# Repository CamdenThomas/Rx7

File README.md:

# Rx7

The record of one 1982 Mazda RX-7: every fact about the car and every project on it, as
self-describing CSV, checked by one tool, read and answered through one app.

```
python tools/rx7.py status
```

- **`CLAUDE.md`** — the entire instruction set for any agent working here. No skills,
  no slash commands, no second document.
- **`tools/rx7.py`** — the only tool. Stdlib Python. `check` is the gate: exit 1 means
  the record contradicts itself, and it is the only thing that can stop a commit.
  `status` prints READY and BLOCKED per area — what can be started now, and what each
  waiting row waits on. `export` is the whole record as JSON for the app; `answer` is the
  one writer of Camden's answers. `selftest` tests the gate resolver and that writer.
- **The Rx7 app** (`02-APP/app/`) — a desktop app for each desk the tree is cloned to
  (Fedora, the Mac) and an Android app for the phone, one design. It shows the car, the projects, the open blocks,
  parts picks, work lists and every decision, and it is where Camden answers. It keeps no
  fact of its own. Its README says how to build and install it.
- **`.github/workflows/rx7.yml`** — CI backstop, `selftest` + `check`, for the clone
  where the hook was never installed.

Areas: `00-CAR` (the car as it stands, and every truth about it), `02-APP` (the app),
`02-PROJECTS/*` (work in flight), `99-ARCHIVE` (finished process, and the v2 view layer this
version replaced). The source files themselves (manuals, catalogues, datasheets) are kept out of git in
`00-CAR/library`, the found 3D models in `02-PROJECTS/03-cad/model` (D-573).

There are no Markdown pages to read or to write in (D-405): blocks, answers, picks, the
TODO lists and every decision's text live in the record, and the app shows them. The only
generated files are the harness-leg drawings (`rx7.py diagrams`, D-385).

One-time per clone: `git config core.hooksPath .githooks`

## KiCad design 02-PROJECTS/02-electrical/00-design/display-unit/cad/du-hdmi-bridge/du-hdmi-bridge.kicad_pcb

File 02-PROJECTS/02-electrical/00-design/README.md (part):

# 00-design — drawn and written by hand, outside the record

*Rev 2026-10-15 (D-611: the parts, each holding its own cad, data, diagrams and firmware; every script
in tools/ · D-612: the boxes' part folders, the CAD marked outdated by the overhaul) · owns: the boundary between this folder and the record, what each folder in it is, and the
rules for the drawings and the code. It lives inside `02-electrical`, which owns every part drawn here.*

## Contents

1. The folders · 2. The fence · 3. Version and the bring-up log · 4. The boards · 5. Why a
schematic at all · 6. Checking the sheets against the record · 7. The firmware · 8. Building the
simulator · 9. Building for the Teensy · 10. What the renderer guarantees · 11. The bench
stages · 12. The bench mule · 13. The design in 3D for the app

---

## 1 · The folders (D-496, D-497, D-611)

One folder per part, each holding the same four kinds of thing, and four shared folders. The parts
are the boxes of the record's `boxes` table (D-612) - the PMU box, the DU, the CU (the CUR is a part
of the CU and sits inside it), the bin box, the bay junction and the amplifier dock - and the
harness. Paths in this README are from this folder.

> **The CAD is outdated by the overhaul (D-612).** The record now holds the boxes, their plugs and
> cavities and the PMU box's connections; every board, mock-up and enclosure below is the last drawn
> state from before it, kept until its CAD-pass row redraws it (Y69 to Y75, the 3D Y77). The pass's
> brief is `diagrams/overhaul-plan.html`. Each part's `diagrams/` holds its **plan sheet**, `<box>-plan.svg`,
> drawn from the record by `rx7.py diagrams` (D-613): that is the current plan; a CAD drawing still
> carries an orange OUTDATED banner (`tools/stamp_outdated.py`).

```
00-design/
├── control-unit/                 THE CONTROL UNIT (CU)
│   ├── cad/                      cu-carrier (KiCad), cu-face-board (KiCad), cu-assembly (the whole unit, FreeCAD)
│   ├── data/                     the boards' BOMs and fab BOMs, their extracts (*-board.json, *-probe.json),
│   │                             the assembly's and the enclosures' parameter tables (*_params.py)
│   ├── diagrams/                 schematic SVGs, renders, assembly drawings, the assembly's views, the face concept
│   ├── firmware/                 cu
│   └── control-unit-remote/      THE CUR, a part of the CU
│       ├── cad/                  cur-board (KiCad), cur-assembly (FreeCAD)
│       ├── data/                 its BOM, its assembly's parameter table
│       └── diagrams/             its schematic, renders, views, the face concept
├── display-unit/                 THE DISPLAY UNIT (DU)
│   ├── cad/                      du-carrier (KiCad), du-hdmi-bridge (KiCad), du-assembly (FreeCAD)
│   ├── data/                     as the CU's
│   ├── diagrams/                 as the CU's
│   ├── firmware/                 du, du_radio, du_sim, tach_simulator
│   └── vendor/                   Bridgetek's ME817EV datasheet (S-500)
├── pmu/                          THE PMU BOX (D-596 to D-610): the PMU, its smart switches, fuses and
│   │                             wake circuit, and at the swap the ECU - its contents in the record (D-612)
│   ├── cad/                      (its board, enclosure and mock-up, Y69)
│   ├── data/                     (its parameter tables, Y69)
│   ├── diagrams/                 (its drawings)
│   ├── firmware/                 pmu_sim (the bench stand-in), ladder_decode_test
│   └── vendor/                   ECUMaster's manual, pinout and CAD package with the STEP (S-027, S-028, S-029)
├── bin-box/                      THE BIN BOX beside the battery (D-608, D-609): cad, data, diagrams - Y73
├── bay-junction/                 THE BAY JUNCTION, the jump post and power junction (D-609): cad, data, diagrams - Y74
├── amp-dock/                     THE AMPLIFIER DOCK and its upmix board (D-609): cad, data, diagrams - Y75
├── harness/
│   ├── cad/connectors/, devices/ what the harness's connectors and devices are drawn from (READMEs; §13)
│   ├── data/                     (reserved)
│   └── diagrams/                 the harness-leg drawings, generated by rx7.py diagrams (D-385)
├── data/                         what the parts share: pin_tables.csv (the vendor pin tables check.py
│                                 holds every symbol to) and the bench order's three cart files
├── diagrams/                     what spans the parts: overhaul-plan.html, the CAD pass's brief (D-612), and
│                                 boxes-plan.svg, the boxes' overview (drawn by rx7.py diagrams, D-613)
├── tools/                        every script (below)
├── tests/                        the host suites and run.sh, which test every part together (tests/README.md)
└── sim/                          the ngspice decks (sim/README.md)
```

**Where a file goes.** A KiCad project or a FreeCAD model, and what is generated from it to be
built (the gerbers and their zip in `cad/<board>/fab/`, STEP, STL, FCStd), is `cad/`. Anything a
tool reads or writes as data - a BOM, a board's extract, a parameter table, a report - is `data/`.
Anything read by eye - SVG, PNG, HTML - is `diagrams/`. No file is in two places: a BOM exported
from a sheet, a fab BOM built from it by `fab_bom.py`, a cart written by `bench_cart.py` each say
in their tool which file they come from.

**The tools** (`tools/`, every one finds a part's files through `parts.py`, where the layout is
written once):

| Script | What it does |
|---|---|
| `parts.py` | the layout: each part's folder, each board's and assembly's files |
| `check.py` | holds every sheet to the record and to `data/pin_tables.csv` (§6) |
| `mockup.py`, `mockup_selftest.py` | build or self-test one unit's mock-up: `freecadcmd tools/mockup.py --pass du-assembly` |
| `du_assembly.py`, `cu_assembly.py`, `cur_assembly.py` | each unit's mock-up geometry, from its `<part>/data/<name>_params.py` |
| `enclosure.py`, `enclosure_lib.py`, `enclosure_extract.py` | a board's enclosure (Y7) from `<part>/data/<board>_enclosure_params.py`; the board extract it reads |
| `du_hdmi_bridge_sch.py` / `_pcb.py`, `cur_board_sch.py` / `_pcb.py` | the two boards drawn by script: the sheet, then the board |
| `fabpack.py`, `assembly.py`, `fab_bom.py`, `bench_cart.py` | a board's fab package, its assembly drawings, its fab BOM against its sheet and the carts, the carts |
| `stamp_outdated.py` | the OUTDATED banner on a CAD drawing the overhaul made stale (D-613); `--clear` takes it off, a re-export drops it |
| `export_glb.py`, `export_glb_fc.py`, `harness_connectors.py`, `harness_devices.py`, `harness_devices_fc.py` | the design in 3D for the app (§13) |

Names (D-611): the DU, CU, CUR and PMU name every folder, project and sketch here; the record's
ids are unchanged (D-496: the module ids ICU and DCU, `icu_channels`, `dcu_channels`, the CAN
senders and the firmware's own identifiers), and only the words a tool prints or a drawing shows
say DU and CU.

## 2 · The fence

**This is not the visual layer.** CLAUDE.md §1 and §9 say the tree has exactly one
generated document and that the visual layer of the record is a separate, later concern
that must not be started yet. Nothing in the CAD is generated, nothing in here renders the
record, and nothing in the drawings reads a CSV at build time. The CAD is a tool being used to
draw circuit boards, in the same category as the firmware — engineering artefacts for one
component, not a view of the design.

The fence, in full:

- **This folder is not an area.** No `data/_tables.csv`, so `rx7.py` does not see it
  at all: `areas()` cannot find it, `check` never reads it, and nothing here can make the
  record invalid or be made invalid by it. It sits in `02-electrical/`, beside `data/`, and
  never inside it (the CAD moved here 2026-09-23, D-386).
- **The boards live in their parts (D-496, D-497, D-611).** The Control Unit's (`control-unit/cad/`:
  the CU carrier, the face board and the unit's mock-up; the CUR's board and mock-up in
  `control-unit/control-unit-remote/cad/`) and the Display Unit's (`display-unit/cad/`: the DU
  carrier, the HDMI bridge and the unit's mock-up) are drawn under this same fence; `tools/` keeps
  every script and `data/` what the parts share.
- **The record wins, always.** If a schematic and a row disagree, the row is right and the
  drawing is stale. Nothing in `../data/` cites a file in here as evidence.
- **A fact worth keeping is promoted, not linked** — it becomes a row, and the drawing
  becomes an illustration of the row.
- **Who draws (D-453).** Camden ruled on 2026-09-12 that he would draw these himself to learn
  KiCad; D-453 lifts that, and the agent draws, lays out and checks the boards too. They are
  still not a view layer: if one starts to look like it, delete it, don't grow it.
- **The firmware is a source of truth** (R6). `display-unit/firmware/du/cluster_core.h` defines
  the palette, every layout constant, the icon set, unit conversions and sensor-fault rendering
  (D-151…D-158). `display-unit/firmware/du/stats.h` owns the automated trip and lifetime figures
  (D-163). `display-unit/firmware/du/can_map.h` is the machine-readable CAN map. The prose
  documents describe *why*; this code defines *what*. It owns, in code: cluster layout, palette,
  rendering, CAN structs and the automated trip figures.

## 3 · Version and the bring-up log

`ICU_FW_VERSION` in `display-unit/firmware/du/du.ino`, `DCU_FW_VERSION` in
`control-unit/firmware/cu/cu.ino` and `PMU_SIM_VERSION` in `pmu/firmware/pmu_sim/pmu_sim.ino`,
printed at boot. Bump it on any behaviour change, log it in `../data/bringup_log.csv`
(`rx7.py add 02-PROJECTS/02-electrical bringup_log …`), tag the commit.

## 4 · The boards

| Project | What | Status |
|---|---|---|
| `control-unit/cad/cu-assembly/` | The Control Unit (D-479, D-480; its box stepping up behind the face, D-604): a parametric FreeCAD mock-up of its insides and its case - face, panel board, DCU carrier, upper connector board, four DT13s in two rows | **OUTDATED by the overhaul (D-612): redrawn at Y70.** **mock-up built, fit check clear, self-test 57 of 57 (2026-10-15)** - one table of numbers (`control-unit/data/cu_assembly_params.py`), built by `tools/mockup.py --pass cu-assembly`, nothing measured (R11); not the print-ready model (F1) |
| `control-unit/control-unit-remote/cad/cur-assembly/` | The Control Unit Remote (D-586, D-602, D-615): the CUR board behind the ruled 43.11 x 32 face in a two-part case - a front shell (faceplate and walls) with a ledge the board rests on, caps with flanges, the encoder's bushing through the face, a rear cover whose posts hold the board and whose grommet takes the pigtail to the inline DRC 24 | **mock-up built, fit check clear, self-test 13 of 13 (Y71, 2026-10-15)** - shell 41.91 x 30.8, 19.6 deep (30.7 with the knob), 7.7 cm3 ASA; one table of numbers (`control-unit/control-unit-remote/data/cur_assembly_params.py`), built by `tools/mockup.py --pass cur-assembly`; nothing measured (R11) |
| `display-unit/cad/du-assembly/` | The ICU as one unit (D-491): a parametric FreeCAD mock-up - the 12.3-inch display behind its bezel, the display plate with the BT817 board and the chain-ii driver boards, the ICU carrier behind (or under) them with the radio's RF window, the page button, DP-ICU-A / -B in the rear plate | **OUTDATED by the overhaul (D-612): redrawn at Y72.** **mock-up built, fit check clear, self-test 34 of 34 (2026-10-15)** - one table of numbers (`display-unit/data/du_assembly_params.py`); 335 x 136.5 face, 206.6 deep with plugs (182.5 carrier below); nothing measured (R11), `C4` / `M-1` the envelope; not the print-ready model (F1) |
| `display-unit/cad/du-carrier/` | The ICU carrier board as a KiCad 10 schematic, plus its Teensy socket footprint | **OUTDATED by the overhaul (D-612): redrawn at Y72.** **provisional board placed, routed, poured and 3D-modelled, DRC clean (F9 / F10, 2026-10-09)** — 110 × 80 mm is `confirm` until `C4` / `F11`; guide step 8 reached, the fit test is `F11`; sheet and board rev 0.04 (`Y42`, 2026-10-13: the two TVS diodes turned to their mark, the tach zener's cathode joined, C1 68 µF 63 V - its README) |
| `display-unit/cad/du-hdmi-bridge/` | The display bridge board (`P119`, Y46, D-550, D-561): a TI TFP410 from the BT817 board's 50-way flat cable (J1 pin k = CN1 pin 51-k, a type-A cable) to an HDMI socket for the panel kit's driver board; 5 V in, AP2112K-3.3; drawn and routed by `tools/du_hdmi_bridge_sch.py` / `tools/du_hdmi_bridge_pcb.py` (freerouting) | **rev 0.01, 62 x 46 mm two layers, ERC 0, DRC 0 / 0 / 0** - its place in the unit and its 5 V source not drawn, confirm; ordered at Y48 |
| `control-unit/cad/cu-carrier/` | The DCU carrier (`H-002`) | **OUTDATED by the overhaul (D-612): redrawn at Y70.** **provisional board placed, routed, poured and 3D-modelled, DRC clean (Y5, 2026-10-09)** — every pin in `dcu_channels.teensy_pin`, the slow lines on a TCA9539-Q1; 180 × 80 mm is `confirm` until `V-102` and luxury `W-332`; `Y11` (2026-10-09) drew the open blocks' worst case DNP: a second expander, the A/C clutch stage and pressure ADC, the radar alert input, the third comfort ground; rev 0.04 carried the 26-way ribbon header (D-458): `Y12` (2026-10-11) re-laid the top-left block for it, H1 now at (4, 15); sheet and board rev 0.05 (`Y42`, 2026-10-13: Q3 on a SOT-23's real pins, the four TVS diodes turned to their mark, C1 / C8 / C29 68 µF 63 V - its README) |
| `control-unit/cad/cu-face-board/` | The Control Unit's face board (`H-008`, D-492; the face itself D-602): the centre encoder with push, the screen's header, four keys and two window switches on a 4 × 3 matrix, two seat encoders, the IS31FL3236A with 24 LEDs, the 26-way ribbon `J1` and the left plate's 2 × 6 header `J3` | **OUTDATED by the overhaul (D-612): redrawn at Y70.** **rev 0.04 provisional board drawn, routed and poured to D-492 (Y20, 2026-10-13)** — ERC 0, DRC 0 / 0 / 0 parity, `check.py --board cu-face-board` 0 mismatches; 180 × 84.76 from the mock-up, `confirm` until `V-113`; the window switches drawn DPDT (the record's DRV up / down share no row or column) and the screen's supply left to `JP1`, both in its README; no processor (D-355), ordered with the DCU's (D-459) |
| `99-ARCHIVE/2026-10-15_upper-board/` | The upper connector board (`P195`), dropped by D-582 when the CU took one header | **archived 2026-10-15 (D-611)** - its sheet, board and fab package kept there as they were |
| `control-unit/control-unit-remote/cad/cur-board/` | The CUR board (`P198`, D-597, D-602, D-604, D-615): 38.11 x 27.0, four layers (In1 GND, In2 +5V_PNL planes), every switch on its cap's centre - the hazard, both winks, the hatch and fuel-door keys, a 4-way mirror switch, a 9 mm encoder; an IS31FL3218 (0x54) and a PCA9555 (0x20) on its AP2112K; the pigtail's nine pads, DP-CUR pin for pin; drawn whole by `tools/cur_board_sch.py` / `_pcb.py` | **rev 1.00 (Y71, 2026-10-15)** - ERC 0, DRC 0 / 0 unconnected / 0 parity, `check.py --board cur-board` 26 checks 0 mismatches; fab package (16 files) in `cad/cur-board/fab/`; every part a class with a placeholder footprint, `confirm` (R11) |
| `tools/enclosure.py`, `tools/enclosure_lib.py`, `tools/enclosure_extract.py` | The three boards' enclosures (cu-carrier, cu-face-board, du-carrier) as parametric FreeCAD builds: `enclosure_extract.py <board>` writes `<part>/data/<board>-board.json` from the board, `freecadcmd tools/enclosure.py --pass <board>` builds base, DT13 plate and lid (ASA, TE 114-151046 cut-outs, lid gasket groove) from `<part>/data/<board>_enclosure_params.py` into `cad/<board>/enclosure/`, caches `<board>-probe.json`, and fit-checks them against the board STEP; rc 0 = clear | **OUTDATED by the overhaul (D-612): redrawn at Y69 to Y72.** **built on the provisional outlines, fit check clean (Y7, 2026-10-09)** — envelopes `C4` / `V-102` / `V-113` are parameters, `confirm`; STEP / STL outputs are generated and ignored; rebuilt at `F11`, printed at `F1` (CK27) |

**Layout is in, as of 2026-09-21 (D-361).** Camden asked for the full PCB and 3D guide for both
boards, which lifts `display-unit/cad/du-carrier/README.md`'s old "schematic yes, PCB not yet"
(ICU layout was already his step `F2`). Board layout and the 3D model are part of the CAD's job
now. **Ordering boards is still his, and still money** (`F2` for the ICU, `F5` for the DCU), and
nothing in here orders anything. Both boards are this build's (D-374): their specs are
`../data/icu_channels.csv` and `../data/dcu_channels.csv`. Only the loads the DCU drives are the
luxury package's.

## 5 · Why a schematic at all

The analog front end is currently only describable in prose. `icu_channels.csv` row IC01
carries, in its stage column, *"100 Ω 1 W pull-up from the carrier's 5 V behind jumper J1
(fitted) → node → 15 kΩ / 10 kΩ divider (×0.4, 5 V → 2.0 V) → 100 nF → BAT54S to 3V3 /
GND"*. That is precise, complete, and unreviewable — nobody can read that sentence and see
that a clamp is on the wrong side of a resistor. Drawn, it is one glance.

That is the whole argument, and it is narrow. It does not extend to the harness: wire
gauge, colour, bundles, cavities and cut lengths are the record's job and KiCad has no
model for any of them.

And it earned that on the first attempt, which belongs here where the argument is made: drawing
IC01 turned up that **every BAT54S clamp on the board was the wrong way round** - anode to +3V3 and
cathode to ground. The sentence above is silent on direction and reads perfectly either way round.
The picture is not.

## 6 · Checking the sheets against the record (`tools/check.py`, Y3)

`python3 tools/check.py` (from this folder, or from anywhere; `-v` for every pass and the walk it took, `--board du-carrier|cu-carrier|cu-face-board|cur-board`, `--netlists DIR` to reuse exports) runs `kicad-cli sch export netlist` on each sheet, one at a time, and holds the drawing to the record: every pin in `icu_channels.teensy_pin` and `dcu_channels.teensy_pin` on its socket pad and named net, reaching the part the record says (the XIAO's TX, the transceiver's STB, the expander's ports); every `at_the_drop` cavity wired on the board-edge connector and walked through the board to that channel's processor pin; the ribbon against `panel_ribbon` on both boards, with the keys, encoders and thumbstick pins that hang off each conductor and the matrix diodes' direction; `CONVENTIONS.md` §5 (the rails never meet, every BAT54S the right way round); and each functional-block symbol's pin numbers against the vendor pin tables in `data/pin_tables.csv` (part, package, pin, name, source URL and page). On the upper connector board (archived 2026-10-15), which had no processor, every cavity of `DP-DCU-D` and `DP-DCU-E` is held to its `state` (wired, or bare behind a plug), to a net of its own, and to what its `src_note` names: the header for the carrier's J6-J8 / J5 / J3 lead pin for pin, or the `panel_ribbon` line, named as that line. It prints one `board:ref:pin expected X got Y` line per disagreement and a summary line per board; exit 0 clean, 1 any mismatch, 3 kicad-cli missing or a sheet unreadable. `tests/run.sh` runs it after the can_map check, so a schematic that disagrees with the record fails the test suite (skipped with a notice when kicad-cli is absent). The record wins: a mismatch is fixed on the sheet, or in `data/pin_tables.csv` from the datasheet, never by editing the check to pass.

**Transistors and diodes are held to a pin table too (Y42, 2026-10-13).** Pricing the bench order turned up three of one kind on the two carriers, each found by hand: the DCU's Q3 drawn gate / drain / source on a SOT-23 (every SOT-23 FET is gate, source, drain), the ICU's zener D20 with its cathode on the package's unused pin, and six one-way TVS diodes drawn with two anodes, the footprint's cathode mark on ground. So a `Q` is checked against `pin_tables.csv` as a `U` is, with a note if it has no table, and a `D` is checked when a table names its value (the one-way TVS: pin 1 the cathode, the end KiCad's footprint marks). Run on the sheets as they were, it refuses all three (the old Q3 only once its part is named). Counts with it, 2026-10-15: du-carrier 105, cu-carrier 172, cu-face-board 79, cur-board 31.

The left plate's wink check (`check_winks`, Y22, D-499 / D-504) is read from the record too: `J2`'s pins against the `L3-S1` cavities that land on J2 (each wink's NC and common on the pin the row names), the commons off the plate's GND and every J1 net, and one resistor from each switch's NO to J2 pin 3 at the value cavity 11's text gives. No number is typed in it; swapped pins and a wrong value were each refused when tried.

First run, 2026-10-09: every record pin on every sheet matched. The 106 mismatches it reports are all pin-table ones on the DCU - U5-U8 BTS3011TE, U9 BTT6050, U10 BTT6200 and U11 DRV8962 still carry functional-block pin numbers (Y5 redraws them on their real packages) - and the ICU's U8 XIAO, whose symbol has EN and BOOT pins the module does not expose as castellations (IC24).

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
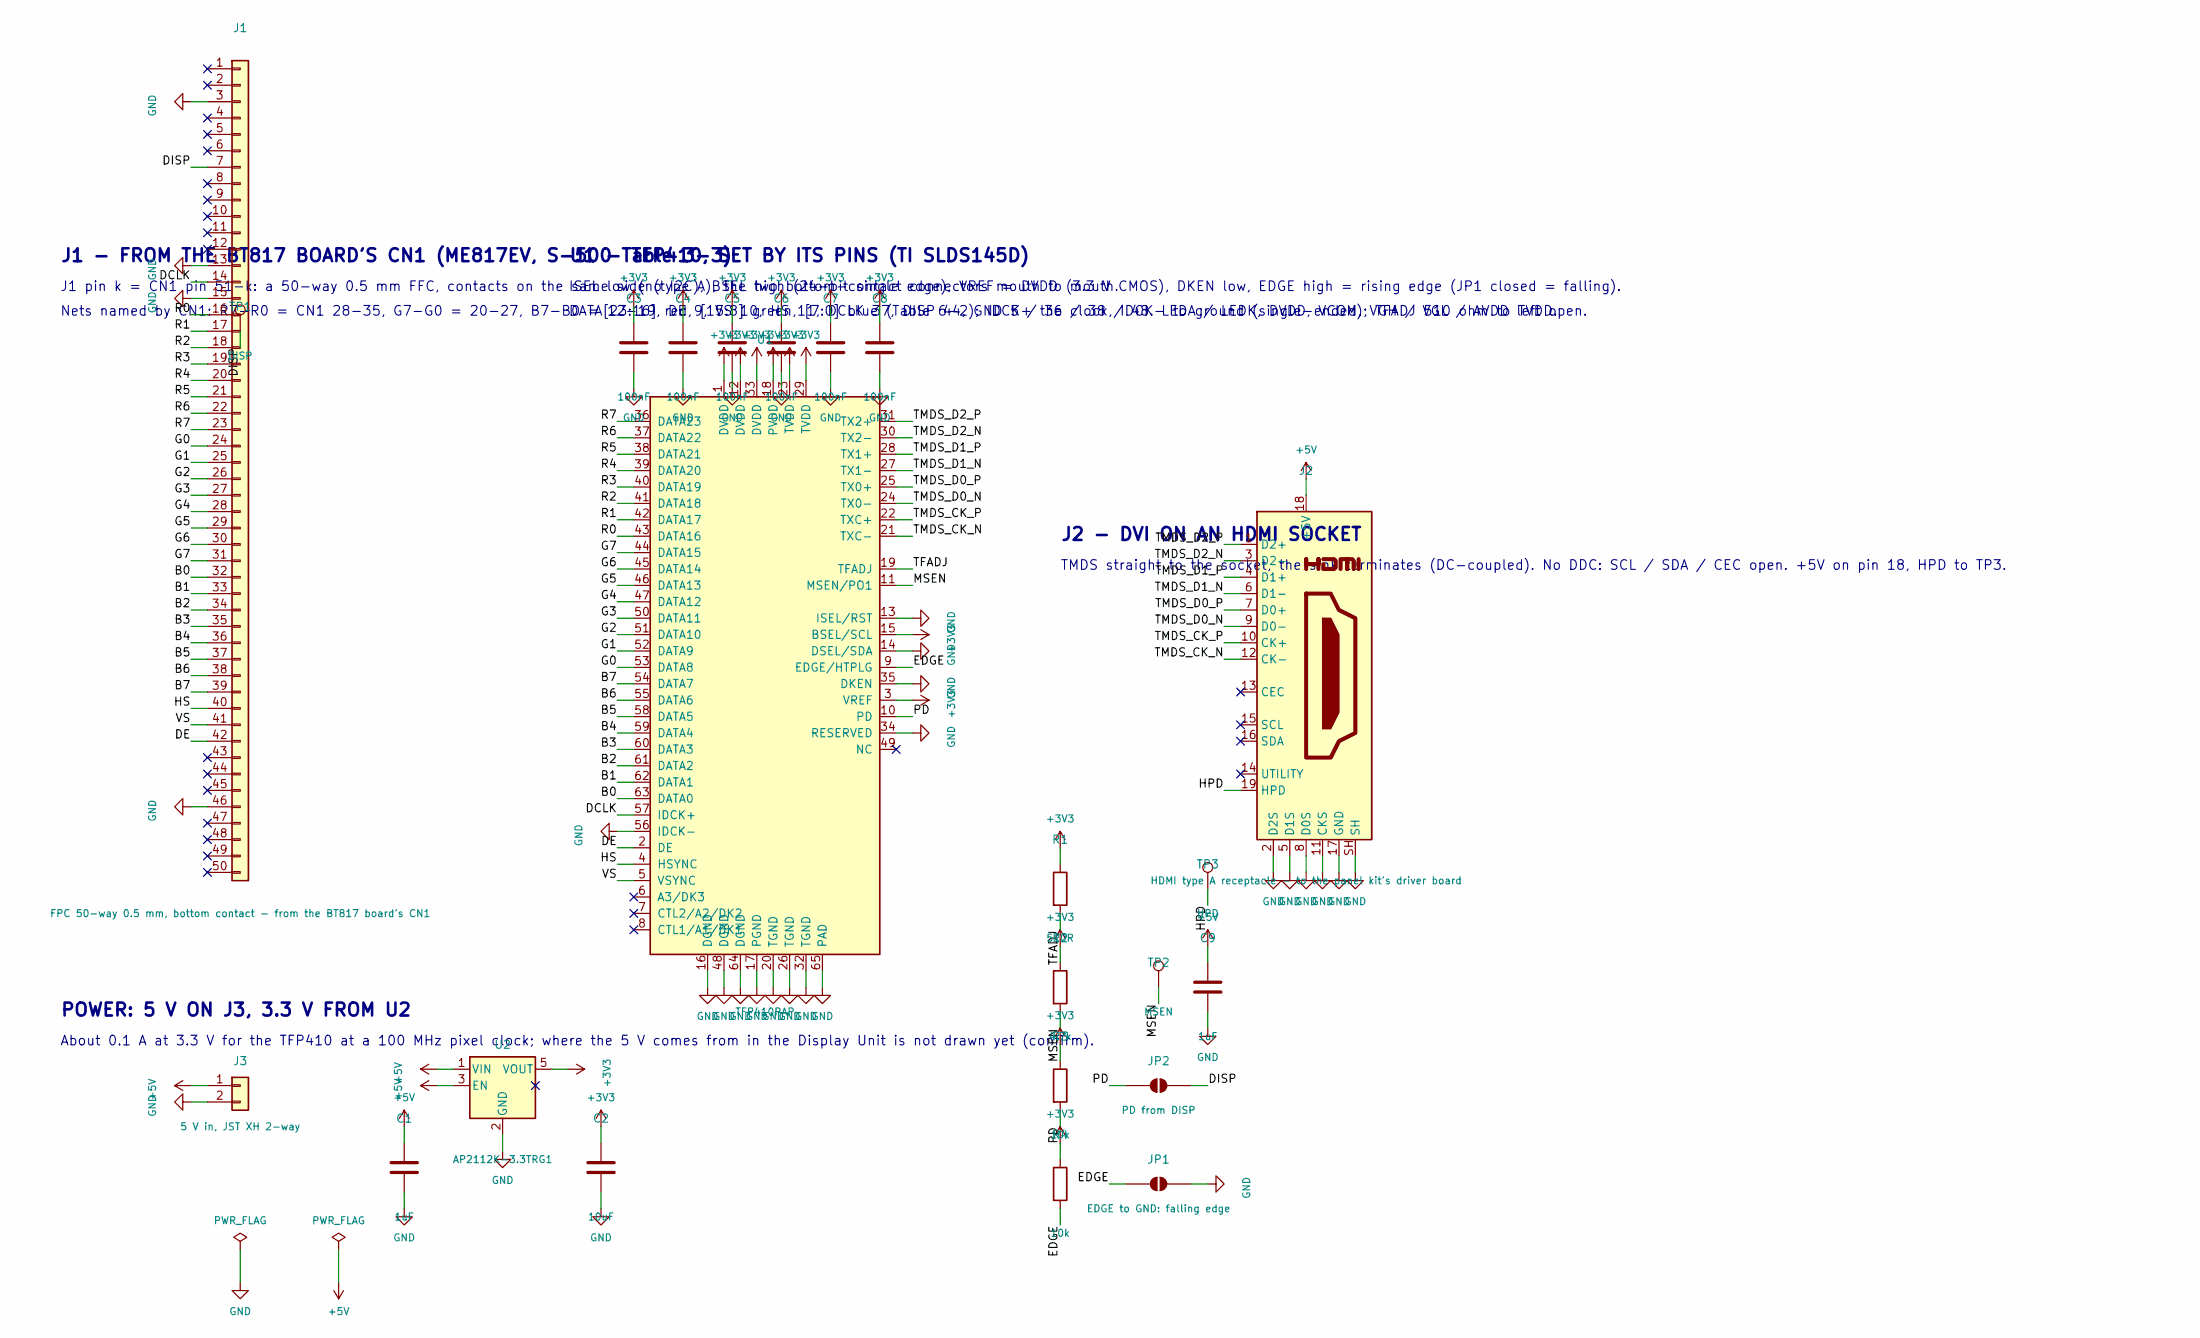
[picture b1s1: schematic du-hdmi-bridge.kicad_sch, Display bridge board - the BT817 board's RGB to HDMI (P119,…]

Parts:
C1, C9: 1uF; C_0603_1608Metric
C2: 10uF; C_0805_2012Metric
C3, C4, C5, C6, C7, C8: 100nF; C_0603_1608Metric
J1: FPC 50-way 0.5 mm, bottom contact - from the BT81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; Hirose_FH12-50S-0.5SH_1x50-1MP_P0.50mm_Horizontal
J2: HDMI type A receptacle - to the panel kit's drive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; HDMI_A_Molex_208658-1001_Horizontal
J3: 5 V in, JST XH 2-way; JST_XH_B2B-XH-A_1x02_P2.50mm_Vertical
JP1: EDGE to GND: falling edge; SolderJumper-2_P1.3mm_Open_RoundedPad1.0x1.5mm
JP2: PD from DISP; SolderJumper-2_P1.3mm_Open_RoundedPad1.0x1.5mm
R1: 510R; R_0603_1608Metric
R2: 4.7k; R_0603_1608Metric
R3, R4: 10k; R_0603_1608Metric
TP1: DISP; TestPoint_Pad_D1.0mm
TP2: MSEN; TestPoint_Pad_D1.0mm
TP3: HPD; TestPoint_Pad_D1.0mm
U1: TFP410PAP; Texas_TQFP-64-1EP_10x10mm_P0.5mm_EP8x8mm_Mask4.44x4.44mm
U2: AP2112K-3.3TRG1; SOT-23-5

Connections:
+3V3: C2.1, C3.1, C4.1, C5.1, C6.1, C7.1, C8.1, R1.1, R2.1, R3.1, R4.1, U1.1 (DVDD), U1.3 (VREF), U1.12 (DVDD), U1.15 (BSEL/SCL), U1.18 (PVDD), U1.23 (TVDD), U1.29 (TVDD), U1.33 (DVDD), U2.5 (VOUT)
+5V: C1.1, C9.1, J2.18 (+5V), J3.1, U2.1 (VIN), U2.3 (EN)
/B0: J1.32, U1.63 (DATA0)
/B1: J1.33, U1.62 (DATA1)
/B2: J1.34, U1.61 (DATA2)
/B3: J1.35, U1.60 (DATA3)
/B4: J1.36, U1.59 (DATA4)
/B5: J1.37, U1.58 (DATA5)
/B6: J1.38, U1.55 (DATA6)
/B7: J1.39, U1.54 (DATA7)
/DCLK: J1.14, U1.57 (IDCK+)
/DE: J1.42, U1.2 (DE)
/DISP: J1.7, JP2.2 (B), TP1.1
/EDGE: JP1.1 (A), R4.2, U1.9 (EDGE/HTPLG)
/G0: J1.24, U1.53 (DATA8)
/G1: J1.25, U1.52 (DATA9)
/G2: J1.26, U1.51 (DATA10)
/G3: J1.27, U1.50 (DATA11)
/G4: J1.28, U1.47 (DATA12)
/G5: J1.29, U1.46 (DATA13)
/G6: J1.30, U1.45 (DATA14)
/G7: J1.31, U1.44 (DATA15)
/HPD: J2.19 (HPD), TP3.1
/HS: J1.40, U1.4 (HSYNC)
/MSEN: R2.2, TP2.1, U1.11 (MSEN/PO1)
/PD: JP2.1 (A), R3.2, U1.10 (PD)
/R0: J1.16, U1.43 (DATA16)
/R1: J1.17, U1.42 (DATA17)
/R2: J1.18, U1.41 (DATA18)
/R3: J1.19, U1.40 (DATA19)
/R4: J1.20, U1.39 (DATA20)
/R5: J1.21, U1.38 (DATA21)
/R6: J1.22, U1.37 (DATA22)
/R7: J1.23, U1.36 (DATA23)
/TFADJ: R1.2, U1.19 (TFADJ)
/TMDS_CK_N: J2.12 (CK-), U1.21 (TXC-)
/TMDS_CK_P: J2.10 (CK+), U1.22 (TXC+)
/TMDS_D0_N: J2.9 (D0-), U1.24 (TX0-)
/TMDS_D0_P: J2.7 (D0+), U1.25 (TX0+)
/TMDS_D1_N: J2.6 (D1-), U1.27 (TX1-)
/TMDS_D1_P: J2.4 (D1+), U1.28 (TX1+)
/TMDS_D2_N: J2.3 (D2-), U1.30 (TX2-)
/TMDS_D2_P: J2.1 (D2+), U1.31 (TX2+)
/VS: J1.41, U1.5 (VSYNC)
GND: C1.2, C2.2, C3.2, C4.2, C5.2, C6.2, C7.2, C8.2, C9.2, J1.3, J1.13, J1.15, J1.46, J2.2 (D2S), J2.5 (D1S), J2.8 (D0S), J2.11 (CKS), J2.17 (GND), J2.SH, J3.2, JP1.2 (B), U1.13 (ISEL/RST), U1.14 (DSEL/SDA), U1.16 (DGND), U1.17 (PGND), U1.20 (TGND), U1.26 (TGND), U1.32 (TGND), U1.34 (RESERVED), U1.35 (DKEN), U1.48 (DGND), U1.56 (IDCK-), U1.64 (DGND), U1.65 (PAD), U2.2 (GND)

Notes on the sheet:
J1 - FROM THE BT817 BOARD'S CN1 (ME817EV, S-500 Table 3-3)
J1 pin k = CN1 pin 51-k: a 50-way 0.5 mm FFC, contacts on the same side (type A), the two bottom-contact connectors mouth to mouth.
Nets named by CN1: R7-R0 = CN1 28-35, G7-G0 = 20-27, B7-B0 = 12-19, DE 9, VS 10, HS 11, DCLK 37, DISP 44, GND 5 / 36 / 38 / 48. LEDA / LEDK, DVDD, VCOM, VGH / VGL / AVDD left open.
U1 - TFP410, SET BY ITS PINS (TI SLDS145D)
ISEL low (no I2C), BSEL high (24-bit single edge), VREF = DVDD (3.3 V CMOS), DKEN low, EDGE high = rising edge (JP1 closed = falling).
DATA[23:16] red, [15:8] green, [7:0] blue (Table 6-2); IDCK+ the clock, IDCK- to ground (single-ended); TFADJ 510 ohm to TVDD.
J2 - DVI ON AN HDMI SOCKET
TMDS straight to the socket, the sink terminates (DC-coupled). No DDC: SCL / SDA / CEC open. +5V on pin 18, HPD to TP3.
POWER: 5 V ON J3, 3.3 V FROM U2
About 0.1 A at 3.3 V for the TFP410 at a 100 MHz pixel clock; where the 5 V comes from in the Display Unit is not drawn yet (confirm).

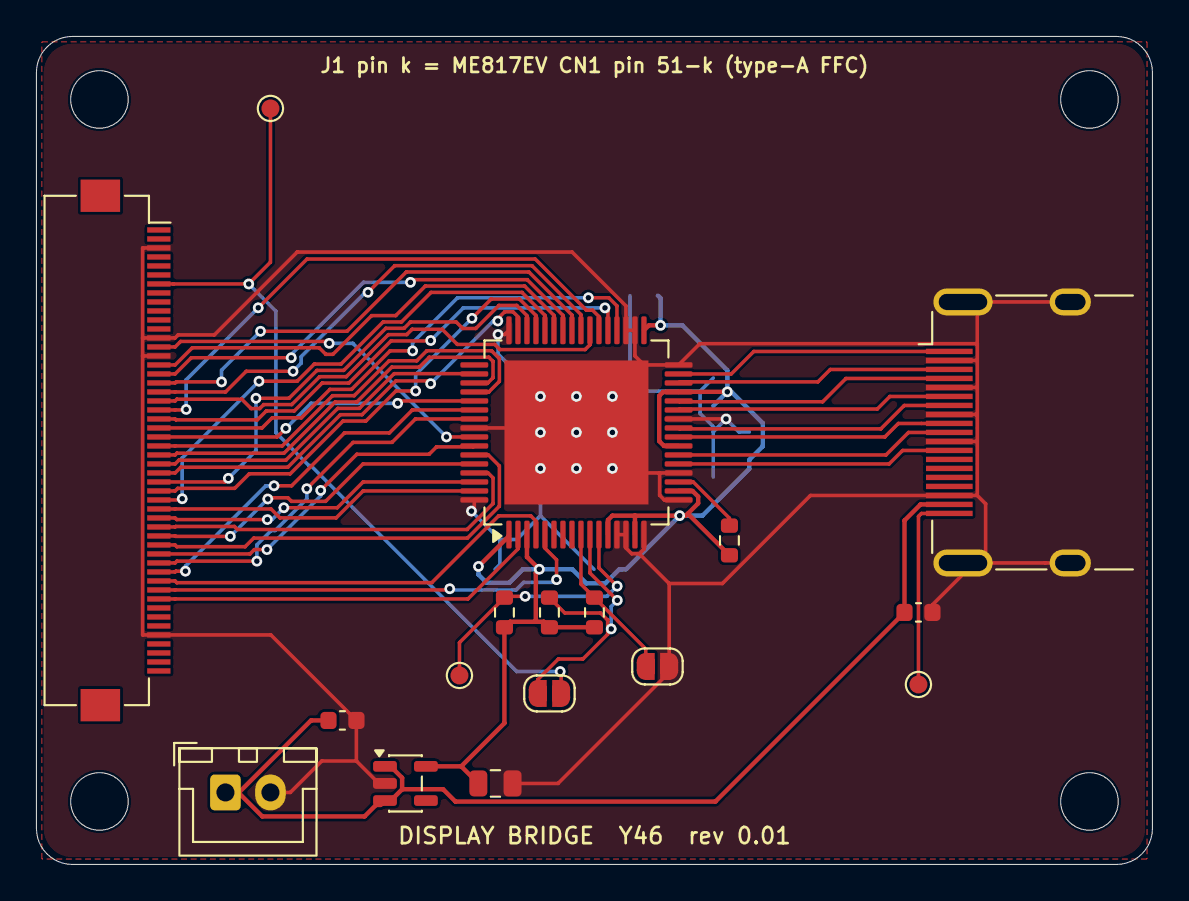
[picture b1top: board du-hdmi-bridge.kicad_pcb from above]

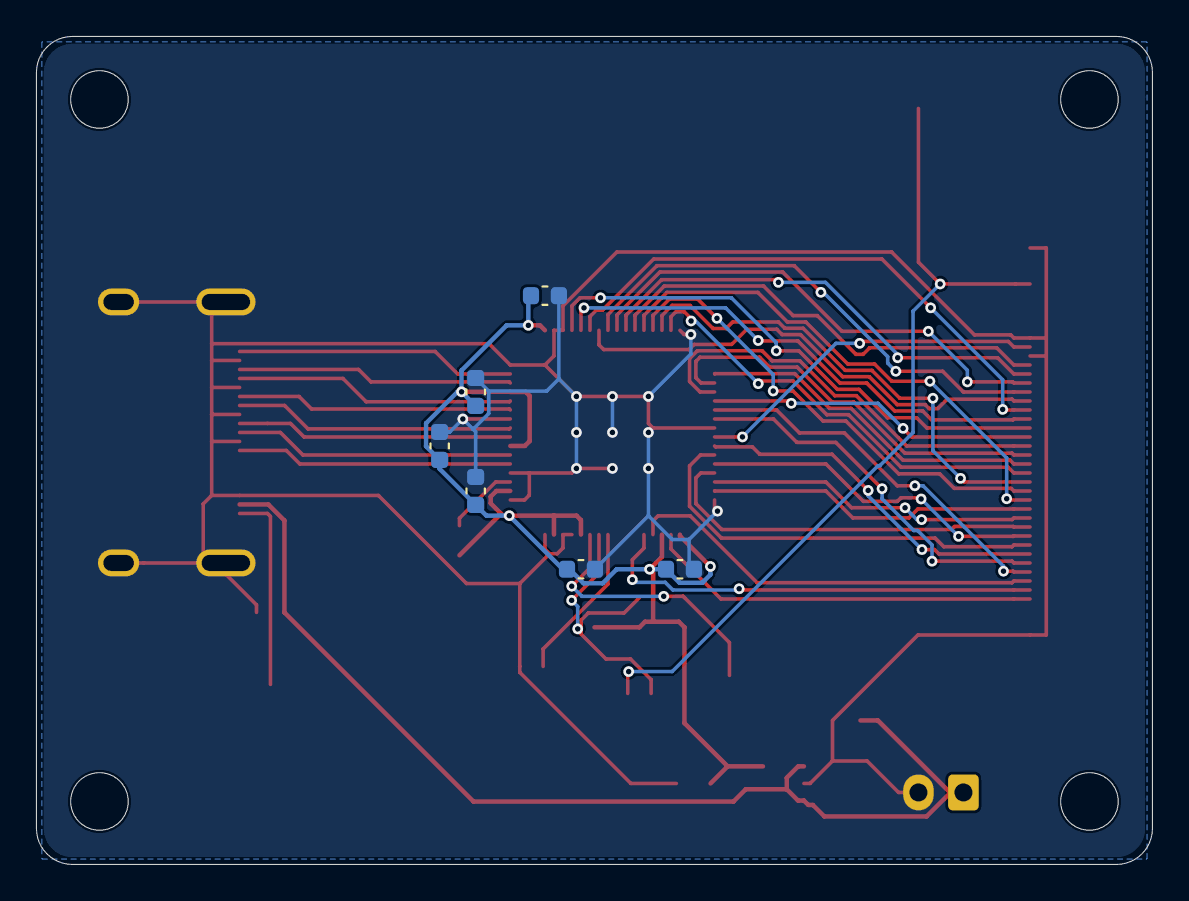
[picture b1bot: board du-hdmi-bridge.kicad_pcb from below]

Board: 2 copper layers, 62.0 x 46.0 mm, 27 parts (6 on the bottom side), 45 nets.

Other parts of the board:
H1, H2, H3, H4: M3; MountingHole_3.2mm_M3

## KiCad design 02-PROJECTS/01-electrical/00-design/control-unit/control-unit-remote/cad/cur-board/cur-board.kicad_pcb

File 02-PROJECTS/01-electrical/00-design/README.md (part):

# 00-design — drawn and written by hand, outside the record

*Rev 2026-10-15 (D-611: the parts, each holding its own cad, data, diagrams and firmware; every script
in tools/ · D-612: the boxes' part folders, the CAD marked outdated by the overhaul) · owns: the boundary between this folder and the record, what each folder in it is, and the
rules for the drawings and the code. It lives inside `01-electrical`, which owns every part drawn here.*

## Contents

1. The folders · 2. The fence · 3. Version and the bring-up log · 4. The boards · 5. Why a
schematic at all · 6. Checking the sheets against the record · 7. The firmware · 8. Building the
simulator · 9. Building for the Teensy · 10. What the renderer guarantees · 11. The bench
stages · 12. The bench mule · 13. The design in 3D for the app

---

## 1 · The folders (D-496, D-497, D-611)

One folder per part, each holding the same four kinds of thing, and four shared folders. The parts
are the boxes of the record's `boxes` table (D-612) - the PMU box, the DU, the CU (the CUR is a part
of the CU and sits inside it), the bin box, the bay junction and the amplifier dock - and the
harness. Paths in this README are from this folder.

> **The CAD is outdated by the overhaul (D-612).** The record now holds the boxes, their plugs and
> cavities and the PMU box's connections; every board, mock-up and enclosure below is the last drawn
> state from before it, kept until its CAD-pass row redraws it (Y69 to Y75, the 3D Y77). The pass's
> brief is `diagrams/overhaul-plan.html`. Each part's `diagrams/` holds its **plan sheet**, `<box>-plan.svg`,
> drawn from the record by `rx7.py diagrams` (D-613): that is the current plan; a CAD drawing still
> carries an orange OUTDATED banner (`tools/stamp_outdated.py`).

```
00-design/
├── control-unit/                 THE CONTROL UNIT (CU)
│   ├── cad/                      cu-carrier (KiCad), cu-face-board (KiCad), cu-assembly (the whole unit, FreeCAD)
│   ├── data/                     the boards' BOMs and fab BOMs, their extracts (*-board.json, *-probe.json),
│   │                             the assembly's and the enclosures' parameter tables (*_params.py)
│   ├── diagrams/                 schematic SVGs, renders, assembly drawings, the assembly's views, the face concept
│   ├── firmware/                 cu
│   └── control-unit-remote/      THE CUR, a part of the CU
│       ├── cad/                  cur-board (KiCad), cur-assembly (FreeCAD)
│       ├── data/                 its BOM, its assembly's parameter table
│       └── diagrams/             its schematic, renders, views, the face concept
├── display-unit/                 THE DISPLAY UNIT (DU)
│   ├── cad/                      du-carrier (KiCad), du-hdmi-bridge (KiCad), du-assembly (FreeCAD)
│   ├── data/                     as the CU's
│   ├── diagrams/                 as the CU's
│   ├── firmware/                 du, du_radio, du_sim, tach_simulator
│   └── vendor/                   Bridgetek's ME817EV datasheet (S-500)
├── pmu/                          THE PMU BOX (D-596 to D-610): the PMU, its smart switches, fuses and
│   │                             wake circuit, and at the swap the ECU - its contents in the record (D-612)
│   ├── cad/                      (its board, enclosure and mock-up, Y69)
│   ├── data/                     (its parameter tables, Y69)
│   ├── diagrams/                 (its drawings)
│   ├── firmware/                 pmu_sim (the bench stand-in), ladder_decode_test
│   └── vendor/                   ECUMaster's manual, pinout and CAD package with the STEP (S-027, S-028, S-029)
├── bin-box/                      THE BIN BOX beside the battery (D-608, D-609): cad, data, diagrams - Y73
├── bay-junction/                 THE BAY JUNCTION, the jump post and power junction (D-609): cad, data, diagrams - Y74
├── amp-dock/                     THE AMPLIFIER DOCK and its upmix board (D-609): cad, data, diagrams - Y75
├── harness/
│   ├── cad/connectors/, devices/ what the harness's connectors and devices are drawn from (READMEs; §13)
│   ├── data/                     (reserved)
│   └── diagrams/                 the harness-leg drawings, generated by rx7.py diagrams (D-385)
├── data/                         what the parts share: pin_tables.csv (the vendor pin tables check.py
│                                 holds every symbol to) and the bench order's three cart files
├── diagrams/                     what spans the parts: overhaul-plan.html, the CAD pass's brief (D-612), and
│                                 boxes-plan.svg, the boxes' overview (drawn by rx7.py diagrams, D-613)
├── tools/                        every script (below)
├── tests/                        the host suites and run.sh, which test every part together (tests/README.md)
└── sim/                          the ngspice decks (sim/README.md)
```

**Where a file goes.** A KiCad project or a FreeCAD model, and what is generated from it to be
built (the gerbers and their zip in `cad/<board>/fab/`, STEP, STL, FCStd), is `cad/`. Anything a
tool reads or writes as data - a BOM, a board's extract, a parameter table, a report - is `data/`.
Anything read by eye - SVG, PNG, HTML - is `diagrams/`. No file is in two places: a BOM exported
from a sheet, a fab BOM built from it by `fab_bom.py`, a cart written by `bench_cart.py` each say
in their tool which file they come from.

**The tools** (`tools/`, every one finds a part's files through `parts.py`, where the layout is
written once):

| Script | What it does |
|---|---|
| `parts.py` | the layout: each part's folder, each board's and assembly's files |
| `check.py` | holds every sheet to the record and to `data/pin_tables.csv` (§6) |
| `mockup.py`, `mockup_selftest.py` | build or self-test one unit's mock-up: `freecadcmd tools/mockup.py --pass du-assembly` |
| `du_assembly.py`, `cu_assembly.py`, `cur_assembly.py` | each unit's mock-up geometry, from its `<part>/data/<name>_params.py` |
| `enclosure.py`, `enclosure_lib.py`, `enclosure_extract.py` | a board's enclosure (Y7) from `<part>/data/<board>_enclosure_params.py`; the board extract it reads |
| `du_hdmi_bridge_sch.py` / `_pcb.py`, `cur_board_sch.py` / `_pcb.py` | the two boards drawn by script: the sheet, then the board |
| `fabpack.py`, `assembly.py`, `fab_bom.py`, `bench_cart.py` | a board's fab package, its assembly drawings, its fab BOM against its sheet and the carts, the carts |
| `stamp_outdated.py` | the OUTDATED banner on a CAD drawing the overhaul made stale (D-613); `--clear` takes it off, a re-export drops it |
| `export_glb.py`, `export_glb_fc.py`, `harness_connectors.py`, `harness_devices.py`, `harness_devices_fc.py` | the design in 3D for the app (§13) |

Names (D-611): the DU, CU, CUR and PMU name every folder, project and sketch here; the record's
ids are unchanged (D-496: the module ids ICU and DCU, `icu_channels`, `dcu_channels`, the CAN
senders and the firmware's own identifiers), and only the words a tool prints or a drawing shows
say DU and CU.

## 2 · The fence

**This is not the visual layer.** CLAUDE.md §1 and §9 say the tree has exactly one
generated document and that the visual layer of the record is a separate, later concern
that must not be started yet. Nothing in the CAD is generated, nothing in here renders the
record, and nothing in the drawings reads a CSV at build time. The CAD is a tool being used to
draw circuit boards, in the same category as the firmware — engineering artefacts for one
component, not a view of the design.

The fence, in full:

- **This folder is not an area.** No `data/_tables.csv`, so `rx7.py` does not see it
  at all: `areas()` cannot find it, `check` never reads it, and nothing here can make the
  record invalid or be made invalid by it. It sits in `01-electrical/`, beside `data/`, and
  never inside it (the CAD moved here 2026-09-23, D-386).
- **The boards live in their parts (D-496, D-497, D-611).** The Control Unit's (`control-unit/cad/`:
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
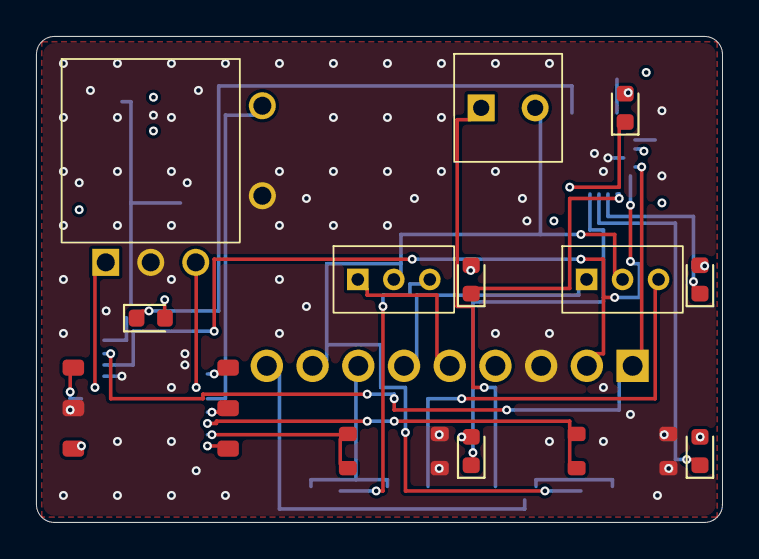
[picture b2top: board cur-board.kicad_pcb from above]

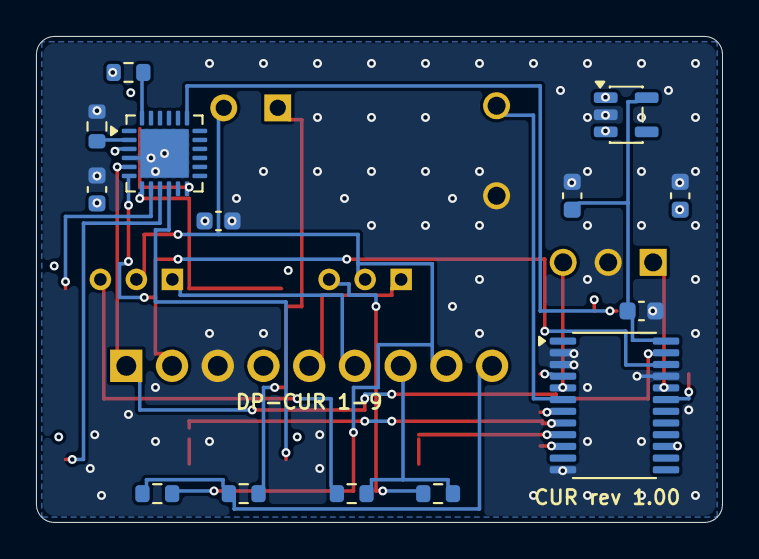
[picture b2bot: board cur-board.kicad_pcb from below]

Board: 4 copper layers, 38.1 x 27.0 mm, 28 parts (15 on the bottom side), 31 nets.

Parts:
C1, C4, C5: 1uF; C_0603_1608Metric
C2, C3: 100nF; C_0603_1608Metric
ENC1: screen knob - 9 mm encoder with push (P219); ScreenKnob_Encoder9mm_Placeholder
J1: pigtail solder pads 1x9 (DP-CUR 1-9); Pigtail_SolderPads_1x09_P2.54mm
LED1: LED 0603 - wink left face (OUT1); LED_0603_1608Metric
LED2: LED 0603 - wink right face (OUT2); LED_0603_1608Metric
LED3: LED 0603 - hatch release symbol (OUT3); LED_0603_1608Metric
LED4: LED 0603 - fuel-door release symbol (OUT4); LED_0603_1608Metric
LED5: LED 0603 - mirror symbol, in the control's well (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; LED_0603_1608Metric
LED6: LED 0603 - hazard red triangle (OUT6); LED_0603_1608Metric
R1: 10k; R_0603_1608Metric
R2: 100k; R_0603_1608Metric
R3: 18k; R_0603_1608Metric
R4: 33k; R_0603_1608Metric
R5: 4.7k; R_0603_1608Metric
R6: 47k; R_0603_1608Metric
SW1: key - hatch; SW_PUSH_TL3342_Placeholder
SW2: key - fuel door; SW_PUSH_TL3342_Placeholder
SW3: wink - left (P204); WinkSwitch_P204_SPDT_Placeholder
SW4: wink - right (P204); WinkSwitch_P204_SPDT_Placeholder
SW5: hazard - latching (P226); HazardSwitch_P226_Latching_Placeholder
SW6: mirror control - 4 way + push (P156); Thumbstick_SKRH_4Way_Push_Placeholder
U1: IS31FL3218-QFLS2-TR; QFN-24-1EP_4x4mm_P0.5mm_EP2.7x2.7mm
U2: PCA9555PW; TSSOP-24_4.4x7.8mm_P0.65mm
U3: AP2112K-3.3TRG1; SOT-23-5

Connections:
+3V3: C3.1, C5.1, U2.24, U3.5
/+5V_PNL: C1.1, C2.1, C4.1, J1.4, LED1.2, LED2.2, LED3.2, LED4.2, LED5.2, LED6.2, R2.1, U1.3, U3.1, U3.3
/HAZ_LADDER: J1.9, R5.1, R6.1
/HAZ_SW: R5.2, SW5.1
/KEY_FUEL: SW2.1, U2.9
/KEY_HATCH: SW1.1, U2.8
/KNOB_A: ENC1.A, U2.20
/KNOB_B: ENC1.B, U2.5
/KNOB_PUSH: ENC1.S1, U2.6
/LED_FUEL: LED4.1, U1.10
/LED_HATCH: LED3.1, U1.9
/LED_HAZARD: LED6.1, U1.12
/LED_MIRROR: LED5.1, U1.19
/LED_REXT: R1.1, U1.2
/LED_SDB: R2.2, U1.24
/LED_WINK_L: LED1.1, U1.7
/LED_WINK_R: LED2.1, U1.8
/MIR_DOWN: SW6.3, U2.15
/MIR_LEFT: SW6.6, U2.10
/MIR_PUSH: SW6.5, U2.7
/MIR_RIGHT: SW6.4, U2.4
/MIR_UP: SW6.1, U2.19
/PNL_SCL: J1.2, U1.6, U2.22
/PNL_SDA: J1.1, U1.5, U2.23
/WINK_COM: J1.8, R6.2, SW3.2, SW4.2, SW5.2
/WINK_L_NC: J1.5, SW3.1
/WINK_L_NO: R3.1, SW3.3
/WINK_REQ: J1.7, R3.2, R4.2
/WINK_R_NC: J1.6, SW4.1
/WINK_R_NO: R4.1, SW4.3
GND: C1.2, C2.2, C3.2, C4.2, C5.2, ENC1.C, ENC1.S2, J1.3, R1.2, SW1.2, SW2.2, SW6.2, U1.4, U1.25, U2.2, U2.3, U2.12, U2.21, U3.2

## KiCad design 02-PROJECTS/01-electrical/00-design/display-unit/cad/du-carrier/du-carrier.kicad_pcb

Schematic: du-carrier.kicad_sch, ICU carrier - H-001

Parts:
C1: 68u 63V; CP_Elec_8x10
C2: 22u 16V; C_1206_3216Metric
C3, C4, C5, C6, C7, C8, C9, C10, C11, C12, C13, C14, C15, C16, C17, C18: 100n; C_0805_2012Metric
C19: 10u; C_0805_2012Metric
C20: 4.7u 100V X7R; C_1210_3225Metric
C21, C22: 220n 100V; C_0805_2012Metric
C23: 22u 10V X7R; C_1206_3216Metric
C24: 100n 16V; C_0805_2012Metric
C25: 1u 16V; C_0805_2012Metric
C26: 20p C0G; C_0805_2012Metric
D1, D2, D3, D4, D5, D6, D7, D8, D9, D10, D21, D22: BAT54S; SOT-23
D20: BZX84C5V1; SOT-23
D23, D25: SL310A; D_SMA
D24, D26: SMBJ33A; D_SMB
D27: MM3Z15VT1G; D_SOD-323
F1: 4 A; Fuse_1206_3216Metric
J1: DRC13-24PA
J2: backlight out; PinHeader_1x02_P2.54mm_Vertical
J4: ME817EV CN8 - 2x8 host header, JP1 2-3 (5 V from 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; PinSocket_2x08_P2.54mm_Vertical
J5: Teensy 4.1 socket - 2 x 24 female headers (D-259); Teensy41_Socket
JP1: J1 FITTED; PinHeader_1x02_P2.54mm_Vertical
JP2: J3 FITTED; PinHeader_1x02_P2.54mm_Vertical
JP3: J7 NOT FITTED; PinHeader_1x02_P2.54mm_Vertical
JP8A1: J8A open collector; PinHeader_1x02_P2.54mm_Vertical
JP8B1: J8B push-pull; PinHeader_1x02_P2.54mm_Vertical
L1: common-mode choke - DNP; fit only with R44 / R45 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; L_CommonModeChoke_Coilank_ACM2012; not fitted
L2: 2.2u XAL4020-222; L_Coilcraft_XAL4020-XXX
Q1: SQD50P06 class, >= 60 V; TO-252-2
Q2: MMBT5551; SOT-23
Q3: DMG3415U class P-FET, SOT-23 - confirm; SOT-23
Q4: MMBT3904; SOT-23
R1, R3, R5, R8, R10, R13, R15, R17, R20, R22, R24, R26, R28, R34, R36, R38, R46, R47: 10k; R_0805_2012Metric
R2, R35, R37, R39, R40: 4.7k; R_0805_2012Metric
R4, R43: 100k; R_0805_2012Metric
R6, R11: 100R 1W; R_2512_6332Metric
R7, R9, R12, R19: 15k; R_0805_2012Metric
R14, R27: 47k; R_0805_2012Metric
R16: 1k; R_0805_2012Metric
R18: 1k - 2.2k 1% ?; R_0805_2012Metric
R21, R23, R25: 22k; R_0805_2012Metric
R29, R30: 100k 0.5W; R_1210_3225Metric
R31: 39k; R_0805_2012Metric
R32: 12k; R_0805_2012Metric
R33: 1.2M; R_0805_2012Metric
R41: 100k 1%; R_0805_2012Metric
R42: 24.9k 1%; R_0805_2012Metric
R44, R45: 0R; R_0805_2012Metric
SW1: IC22; JST_XH_B2B-XH-A_1x02_P2.50mm_Vertical
U1: LMR36015FSCQ-Q1; Texas_RNX0012C_VQFN-14-11-1EP_2x3mm_P0.5mm_EP0.25x1.825mm
U2: VN5E class, >= 6 A - DNP; not fitted
U3: TCAN1042HVDRQ1; SOIC-8_3.9x4.9mm_P1.27mm
U4: LM393; SOIC-8_3.9x4.9mm_P1.27mm
U5: 74LVC1G17; SOT-23-5
U7: Adafruit 4517 LSM6DSOX+LIS3MDL (LSM6DSO class, P1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; IMU_Adafruit_4517_Socket
U8: XIAO ESP32C3 2x7 socket (Seeed, S-490); XIAO_ESP32C3_Socket_2x07

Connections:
+12V_BL: D25.1 (K), D26.1 (K), F1.2
+12V_BL_SW: J2.1, Q1.2 (D)
+12V_LOGIC: C1.1, C20.1, C21.1, C22.1, D23.1 (K), D24.1 (K), U1.2 (VIN), U1.9 (EN), U1.10 (VIN)
/BL_EN: J5.28 (BL_EN), R3.1, R4.1
/BL_FUSED: D27.1 (K), F1.1, Q1.3 (S), R1.1
/BL_GATE: D27.2 (A), Q1.1 (G), R1.2, R2.1
/BT817_INT: J4.14 (INT), J5.16 (BT817_INT)
/BT817_PD: J4.13 (PD), J5.11 (BT817_PD)
/BT_IO2: J4.6 (QSPI_IO2), J5.18 (BT_IO2)
/BT_IO3: J4.5 (QSPI_IO3), J5.19 (BT_IO3)
/BUCK_BOOT: C24.1, U1.4 (BOOT)
/BUCK_FB: C26.2, R41.2, R42.1, U1.7 (FB)
/BUCK_SW: C24.2, L2.1, U1.3 (NC), U1.12 (SW)
/BUCK_VCC: C25.1, U1.5 (VCC)
/CAN2H_J: J1.4, L1.2, R44.2
/CAN2L_J: J1.5, L1.4, R45.2
/CANH_U: L1.1, R44.1, U3.7 (CANH)
/CANL_U: L1.3, R45.1, U3.6 (CANL)
/CAN_RXD: J5.45 (CAN_RXD), U3.4 (RXD)
/CAN_STB: J5.24 (CAN_STB), R5.1, U3.8 (STB)
/CAN_TXD: J5.44 (CAN_TXD), U3.1 (TXD)
/I2C_SCL: J5.41 (I2C_SCL), R39.2, U7.4 (SCL)
/I2C_SDA: J5.40 (I2C_SDA), R40.2, U7.5 (SDA)
/IC01_ADC: C5.1, D1.3 (COM), J5.36 (IC01_ADC), R7.2, R8.1
/IC02_ADC: C6.1, D2.3 (COM), J5.37 (IC02_ADC), R9.2, R10.1
/IC03_ADC: C7.1, D3.3 (COM), J5.38 (IC03_ADC), R12.2, R13.1
/IC04_CAP: J5.4 (IC04_CAP), R33.1, R34.2, U4.1
/IC05_ADC: C8.1, D4.3 (COM), J5.39 (IC05_ADC), R14.2, R15.1
/IC06_DIG: C9.1, D5.3 (COM), J5.20 (IC06_DIG), R16.2, R17.1
/IC07_ADC: C10.1, D6.3 (COM), J5.42 (IC07_ADC), R19.2, R20.1
/IC08_CAP: J5.5 (IC08_CAP), U5.4
/IC08_IN: D22.3 (COM), R36.2, R37.1, U5.2
/IC09_DIG: C11.1, D7.3 (COM), J5.21 (IC09_DIG), R21.2, R22.1
/IC10_DIG: C12.1, D8.3 (COM), J5.22 (IC10_DIG), R23.2, R24.1
/IC11_DIG: C13.1, D9.3 (COM), J5.23 (IC11_DIG), R25.2, R26.1
/IC14_ADC: C14.1, D10.3 (COM), J5.43 (IC14_ADC), R27.2, R28.1
/IC14_IN: J1.2, R27.1
/ICU_B1: J1.7, JP1.1, R7.1
/ICU_B2: J1.8, R9.1
/ICU_B3: J1.9, JP2.1, R12.1
/ICU_B4: J1.6, R29.2
/ICU_B5: J1.11, R14.1
/ICU_B6: J1.10, R16.1
/ICU_B7: J1.13, JP3.1, R19.1
/ICU_B8: J1.14, R35.2, R36.1
/ICU_B10: J1.16, R21.1
/ICU_B11: J1.17, R23.1
/ICU_B12: J1.22, R25.1
/IMU_INT: J5.25 (IMU_INT), U7.11 (INT1)
/PAGE_BTN: C17.1, J5.17 (PAGE_BTN), R38.2, SW1.2
/PG_5V: J5.29 (PG_5V), R43.2, U1.8 (PG)
/RADIO_5V: C19.1, Q3.3 (D), U8.14 (VBUS)
/RADIO_BOOT: J5.27 (RADIO_BOOT), U8.10 (D9/MISO)
/RADIO_EN: J5.26 (RADIO_EN), R47.1
/RADIO_RX: J5.10 (RADIO_RX), U8.8 (D7/RX)
/RADIO_TX: J5.9 (RADIO_TX), U8.7 (D6/TX)
/SPI_CS: J4.2 (QSPI_CS), J5.12 (SPI_CS)
/SPI_MISO: J4.3 (QSPI_IO1), J5.14 (SPI_MISO)
/SPI_MOSI: J4.4 (QSPI_IO0), J5.13 (SPI_MOSI)
/SPI_SCK: J4.1 (QSPI_SCK), J5.35 (SPI_SCK)
unnamed: D20.2 (NC), D20.3 (K), D21.3 (COM), R30.1, R33.2, U4.3 (+)
unnamed: D23.2 (A), J1.1
unnamed: D25.2 (A), J1.3
unnamed: JP1.2, R6.2
unnamed: JP2.2, R11.2
unnamed: JP3.2, R18.2
unnamed: JP8A1.2, R35.1
unnamed: JP8B1.2, R37.2
unnamed: Q2.1 (B), R3.2
unnamed: Q2.3 (C), R2.2
unnamed: Q3.1 (G), Q4.3 (C), R46.2
unnamed: Q4.1 (B), R47.2
unnamed: R29.1, R30.2
unnamed: R31.2, R32.1, U4.2 (-)

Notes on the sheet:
IC10 turn R sense
IC02 oil pressure
IC03 fuel level
DISPLAY AND LOCAL
1 +12 V logic, O10
x0.175 - 12 V becomes 2.1 V
IC22 page button - momentary, by the display
x0.4 - 5 V becomes 2.0 V
2 IC02 oil pressure
IC06 brake warning
IC07 oil temp
500 kbps. NO termination on this board: D-079's far-end 120 ohm moved to the dash node when the engine-bay drop was released (D-318 -> D-346). The common-mode choke is a DNP footprint for that same reason - the field says so, not a comment.
BAT54S is a SERIES pair, A - COM - K, and the direction is the whole point: COM carries the signal, A goes to GROUND so a negative excursion is caught by GND - COM, and K goes to +3V3 so a positive one is caught by COM - +3V3. Drawn the other way round it clamps nothing and puts a diode path from +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
ANALOG IN - one stage, drawn nine times
Trailing coil negative primary: hundreds of volts of inductive kick (luxury D-304). 2 pulses per revolution. The comparator sits on +5 V DELIBERATELY. Its common-mode input range stops about 1.5 V under its supply, so on 3.3 V the 5.1 V zener node would clip and the tach would read nothing above id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
WHAT THIS SHEET DOES NOT KNOW
IC14 illumination ref
5 IC05 charge lamp
THE PROCESSOR BOUNDARY
the value waits on Q-308 - no sender has been chosen, so it is a question mark
IC23 - the I2C pull-ups live here because the bus is board-local
the open-collector output is pulled up to +3V3, NOT to +5 V - that is what lets a comparator running on 5 V drive a 3.3 V-only input safely
11 IC10 turn R sense
read as digital: low means warn
9 spare - nothing on the board reads it (D-271)
DP-ICU-A tail A, DT06-6S from the dash post (D-270)
IC09 turn L sense
U1 - the ICU's 5 V buck in full (work F13; record icu_channels IC12, parts P105 / P159). TI LMR36015-Q1 datasheet SNVSAY8D, typical application for 5 V: every value confirm until the part is chosen. Layout: input caps tight across both VIN/PGND pairs, SW copper short, CBOOT from BOOT to the SW-NC l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
1 IC01 water temp
U1 (the 5 V buck) is drawn in full at the bottom of the sheet (F13).
Two 12 V inputs, and they never meet on this board: two inputs, two diodes (D-273). A net tie joining +12V_LOGIC to +12V_BL is not a drawing error to tidy up later - it is the error the two-diode design exists to prevent.
IC15 - a single pour, star-tied at this pin
~0.8 A peak on +5 V: the Teensy, the transceiver, the IMU, the three sender excitations and the radio (D-273).
8 IC08 road speed
F1 is 4 A because the 900-1000 nit bar and its scaler draw about 2.5 A at 12 V (D-269, D-273).
+3V3 is the Teensy's own 3.3 V output, arriving at the socket. There is NO 3.3 V regulator on this carrier: D-273 put the radio on the XIAO module's own LDO because a BLE scan peaks near 300 mA and the Teensy's regulator is a 250 mA part. TARGET.md section 1 still says 'LDO for the ESP32-C3' - the 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
3 IC03 fuel level
IC11 high beam
POWER
4 CAN2 H

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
